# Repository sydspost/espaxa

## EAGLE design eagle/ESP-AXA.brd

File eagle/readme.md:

Instructions

Download the zip file "Gerber files ESP-AXA_2022-08-22". Use your favorite (chinese) PCB manufactorer to fabricate the PCB.

Size PCB: 75 x 69 mm
Layers: 2 Layers

Keep the rest of the options default

Complete story on https://www.sydspost.nl/index.php/2021/03/15/axa-remote-2-0-raamopener-bedienen-vanuit-domotics/

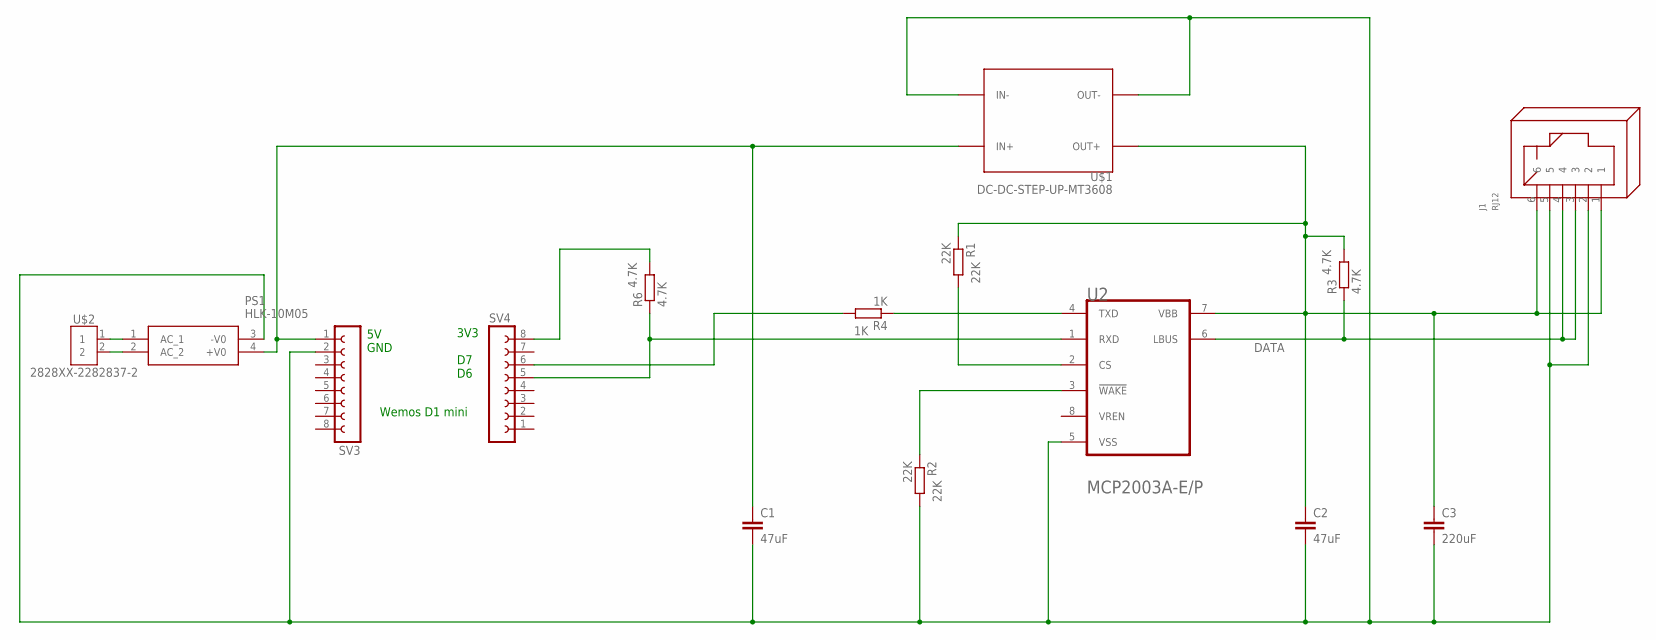
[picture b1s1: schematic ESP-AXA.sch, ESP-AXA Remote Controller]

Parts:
C1, C2: 47uF; C7.5B3
C3: 220uF; C7.5B3
J1: RJ12
PS1: HLK-10M05; HLK10M05
R1, R2: 22K; 0204V
R3, R6: 4.7K; 0204V
R4: 1K; 0204V
SV3, SV4: FE08-1; FE08
U2: MICROCHIP_MCP2003A-E-PMICROCHIP_MCP2003A-E-P_0_0; MICROCHIP_MCP2003A-E-P_0
U$1: DC-DC-STEP-UP-MT3608
U$2: 2828XX-2282837-2; TERMBLK_508-2N

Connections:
5V: C1.1, PS1.4 (+V0), SV3.1, U$1.IN+
8V: C2.1, C3.1, J1.1, J1.6, R1.1, R3.2, U2.7 (VBB), U$1.OUT+
240VAC: PS1.2 (AC_2), U$2.2
CS: R1.2, U2.2 (CS)
DATA: J1.3, J1.4, R3.1, U2.6 (LBUS)
GND: C1.2, C2.2, C3.2, J1.2, J1.5, PS1.3 (-V0), R2.2, SV3.2, U2.5 (VSS), U$1.IN-, U$1.OUT-
unnamed: R4.2, SV4.6
unnamed: R6.2, SV4.8
unnamed: PS1.1 (AC_1), U$2.1
RX: R6.1, SV4.5, U2.1 (RXD)
TX: R4.1, U2.4 (TXD)
WAKE: R2.1, U2.3 (!WAKE!)

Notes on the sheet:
Wemos D1 mini
5V GND
3V3 D7 D6

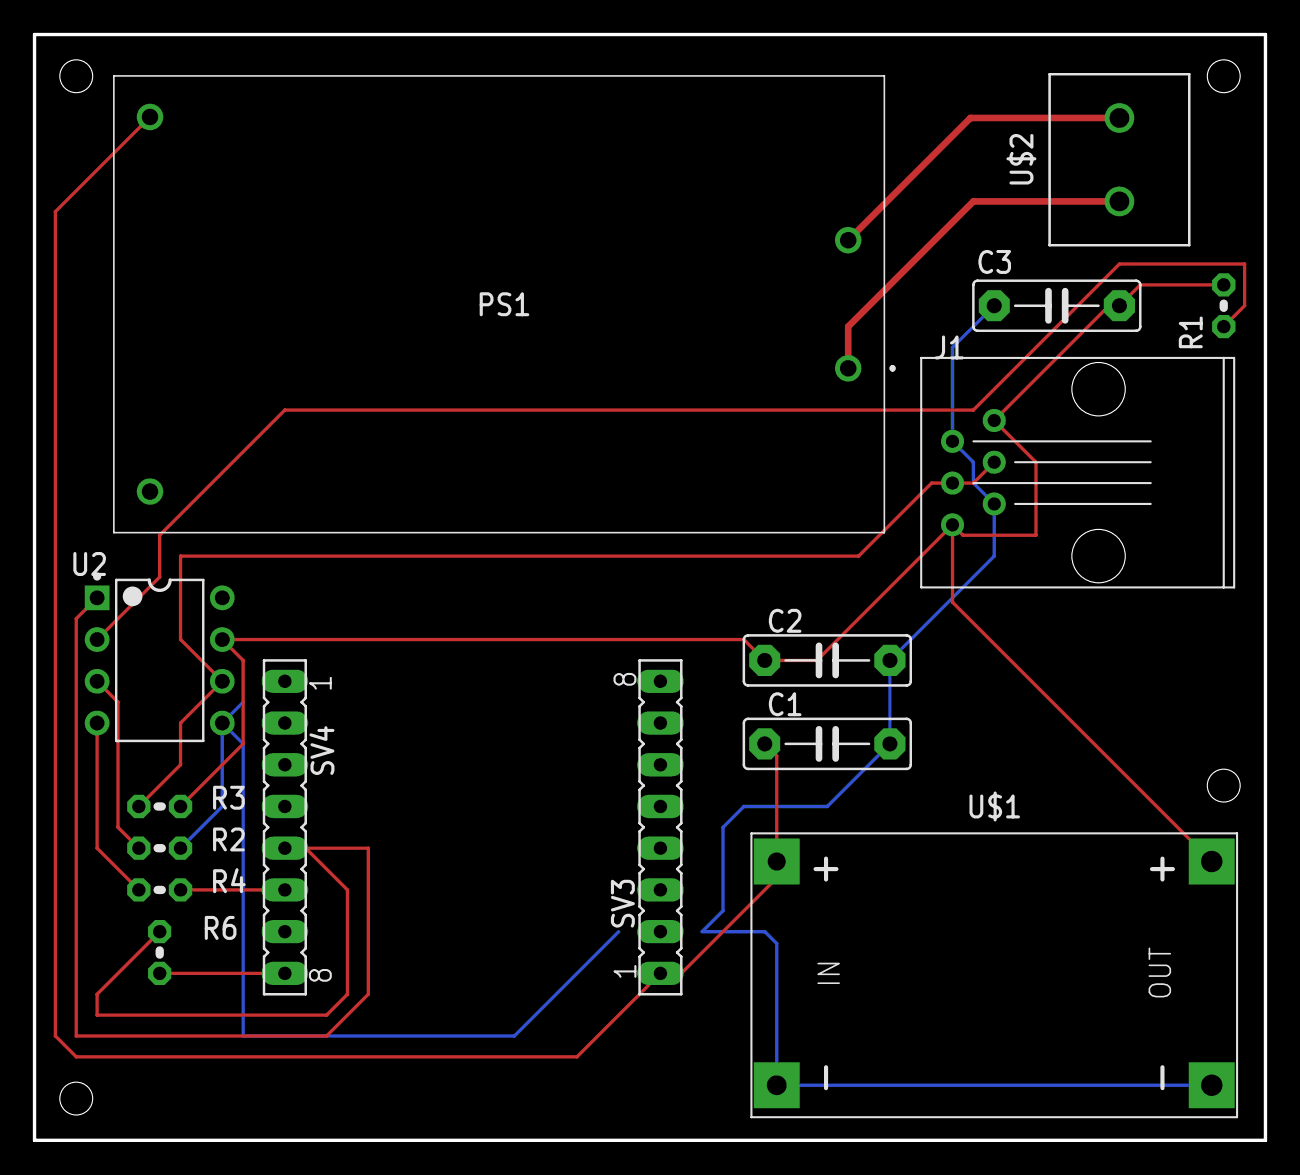
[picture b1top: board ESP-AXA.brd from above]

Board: 2 copper layers, 74.9 x 67.3 mm, 15 parts (0 on the bottom side), 12 nets.
